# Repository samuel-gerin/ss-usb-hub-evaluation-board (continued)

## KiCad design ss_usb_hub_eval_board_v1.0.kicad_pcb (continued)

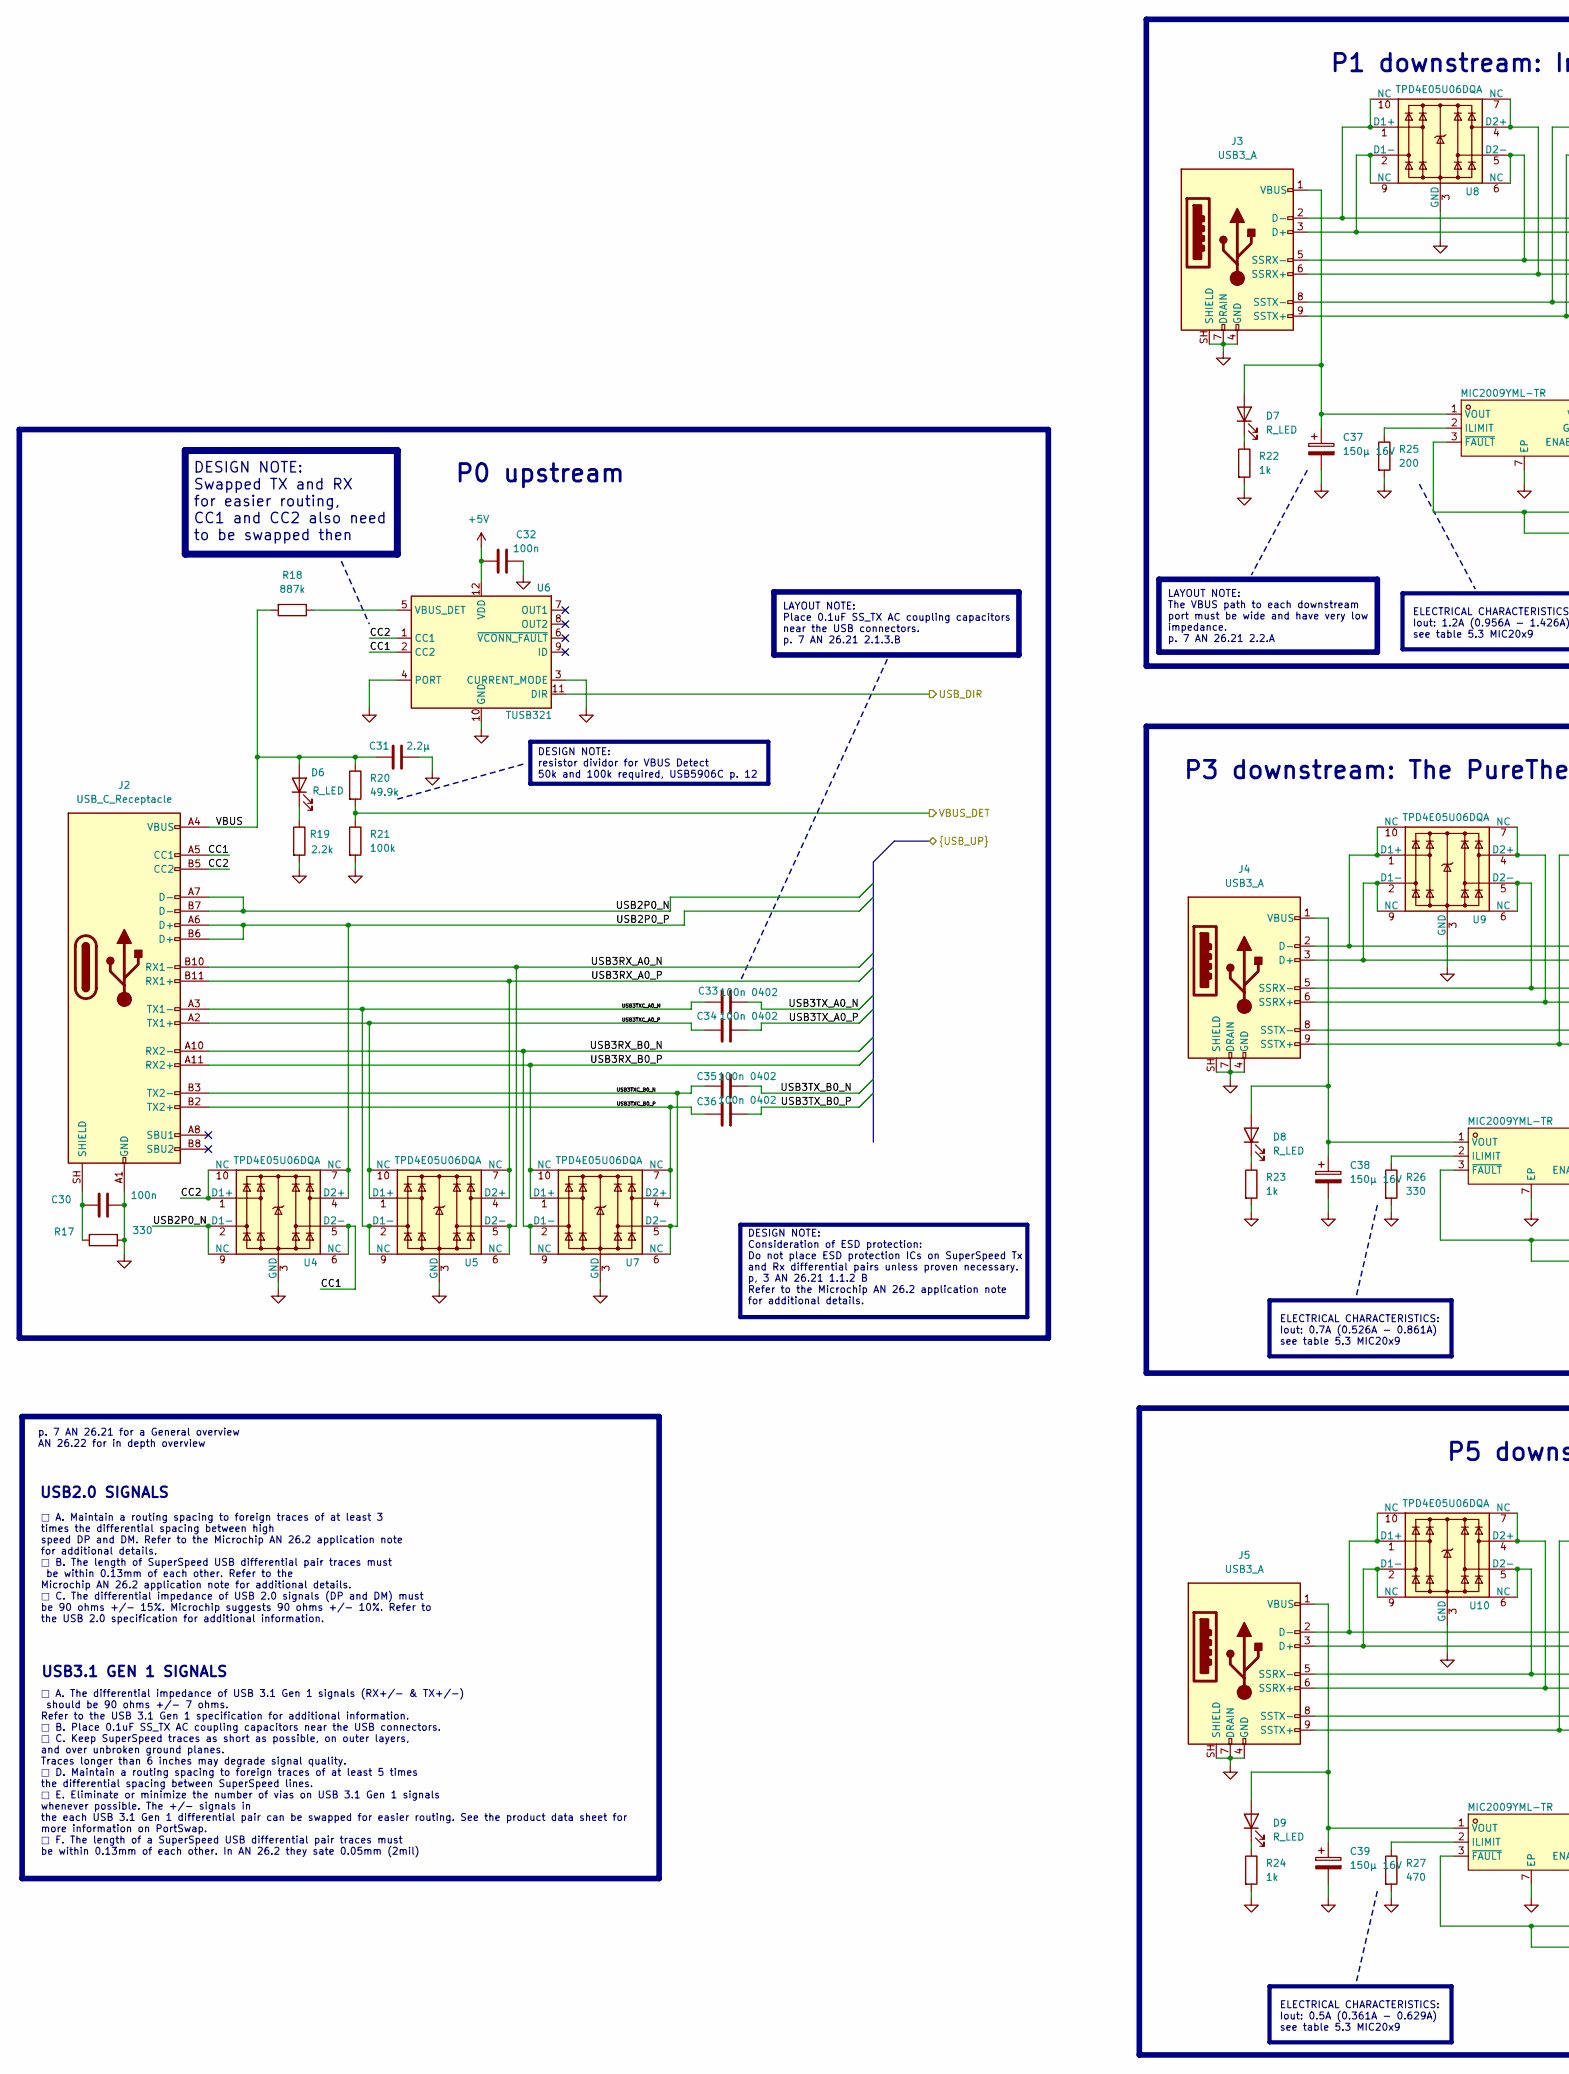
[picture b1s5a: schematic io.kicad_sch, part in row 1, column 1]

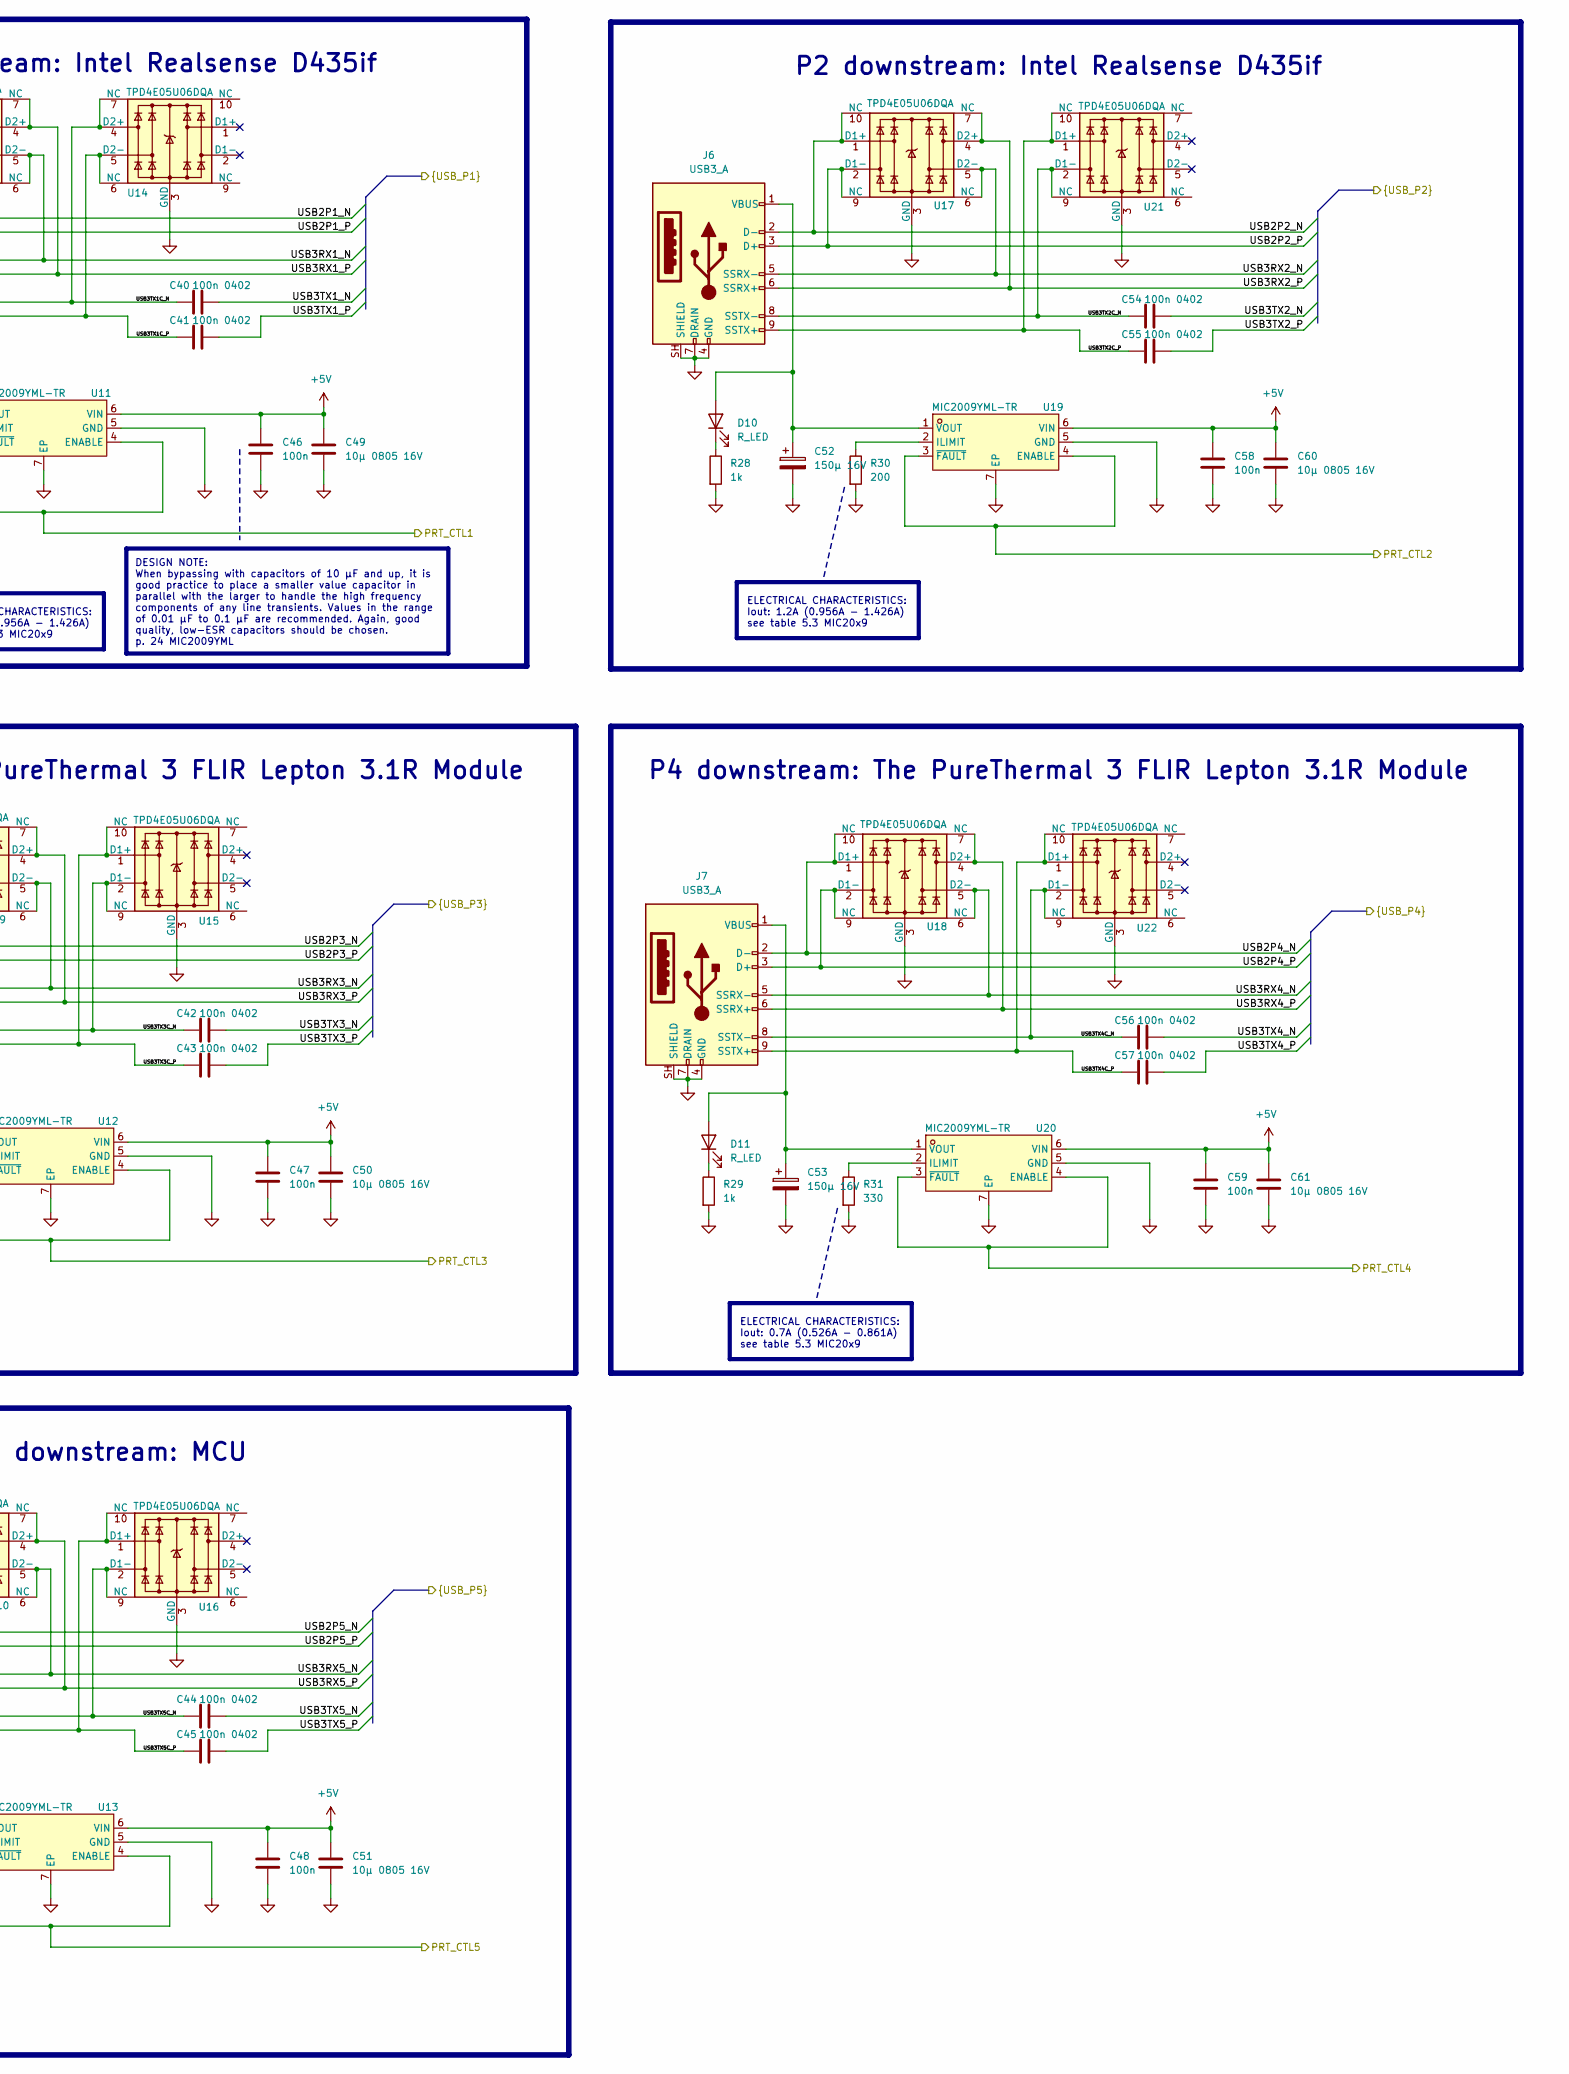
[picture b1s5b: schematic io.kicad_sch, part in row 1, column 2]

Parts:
C30, C32, C46, C47, C48, C58, C59: 100n; C_0603_1608Metric; LCSC C14663
C31: 2.2µ; C_0603_1608Metric; LCSC C23630
C33, C34, C35, C36, C40, C41, C42, C43, C44, C45, C54, C55, C56, C57: 100n 0402; C_0402_1005Metric; LCSC C1525
C37, C38, C52, C53: 150µ 16V; CP_Elec_8x10; LCSC C38513
C39: 150µ 16V; CP_Elec_8x10.5; LCSC C38513
C49, C50, C51, C60, C61: 10µ 0805 16V; C_0805_2012Metric; LCSC C1713
D6, D7, D8, D9, D10, D11: R_LED; LED_0603_1608Metric; LCSC C2286
J2: USB_C_Receptacle; USB-C-SMD_TYPE-C-USB-18; LCSC C134092
J3, J4, J5, J6, J7: USB3_A; USB-SMD_692122030100; LCSC C5355286
R17, R26, R31: 330; R_0603_1608Metric; LCSC C23138
R18: 887k; R_0603_1608Metric; LCSC C246015
R19: 2.2k; R_0603_1608Metric; LCSC C4190
R20: 49.9k; R_0603_1608Metric; LCSC C23184
R21: 100k; R_0603_1608Metric; LCSC C25803
R22, R23, R24, R28, R29: 1k; R_0603_1608Metric; LCSC C21190
R25, R30: 200; R_0603_1608Metric; LCSC C8218
R27: 470; R_0603_1608Metric; LCSC C23179
U4, U5, U7, U8, U9, U10, U14, U15, U16, U17, U18, U21, U22: TPD4E05U06DQA; USON-10_2.5x1.0mm_P0.5mm; LCSC C138714
U6: TUSB321; Texas_X2QFN-12_1.6x1.6mm_P0.4mm; LCSC C139392
U11, U12, U13, U19, U20: MIC2009YML-TR; MLF-6_L2.0-W2.0-P0.65-BL-EP; MPN MIC2009YML-TR; LCSC Part C621495

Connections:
+5V: C32.2, C46.1, C47.1, C48.1, C49.1, C50.1, C51.1, C58.1, C59.1, C60.1, C61.1, U6.12 (VDD), U11.6 (VIN), U12.6 (VIN), U13.6 (VIN), U19.6 (VIN), U20.6 (VIN); also elsewhere on the board
/IO/CC1: J2.A5 (CC1), U4.5 (D2-), U4.6 (NC), U6.2 (CC2)
/IO/CC2: J2.B5 (CC2), U4.1 (D1+), U4.10 (NC), U6.1 (CC1)
/IO/PRT_CTL1: U11.3 (~FAULT), U11.4 (ENABLE); also elsewhere on the board
/IO/PRT_CTL2: U19.3 (~FAULT), U19.4 (ENABLE); also elsewhere on the board
/IO/PRT_CTL3: U12.3 (~FAULT), U12.4 (ENABLE); also elsewhere on the board
/IO/PRT_CTL4: U20.3 (~FAULT), U20.4 (ENABLE); also elsewhere on the board
/IO/PRT_CTL5: U13.3 (~FAULT), U13.4 (ENABLE); also elsewhere on the board
/IO/USB2P0_N: J2.A7 (D-), J2.B7 (D-), U4.2 (D1-), U4.9 (NC); also elsewhere on the board
/IO/USB2P0_P: J2.A6 (D+), J2.B6 (D+), U4.4 (D2+), U4.7 (NC); also elsewhere on the board
/IO/USB2P1_N: J3.2 (D-), U8.1 (D1+), U8.10 (NC); also elsewhere on the board
/IO/USB2P1_P: J3.3 (D+), U8.2 (D1-), U8.9 (NC); also elsewhere on the board
/IO/USB2P2_N: J6.2 (D-), U17.1 (D1+), U17.10 (NC); also elsewhere on the board
/IO/USB2P2_P: J6.3 (D+), U17.2 (D1-), U17.9 (NC); also elsewhere on the board
/IO/USB2P3_N: J4.2 (D-), U9.1 (D1+), U9.10 (NC); also elsewhere on the board
/IO/USB2P3_P: J4.3 (D+), U9.2 (D1-), U9.9 (NC); also elsewhere on the board
/IO/USB2P4_N: J7.2 (D-), U18.1 (D1+), U18.10 (NC); also elsewhere on the board
/IO/USB2P4_P: J7.3 (D+), U18.2 (D1-), U18.9 (NC); also elsewhere on the board
/IO/USB2P5_N: J5.2 (D-), U10.1 (D1+), U10.10 (NC); also elsewhere on the board
/IO/USB2P5_P: J5.3 (D+), U10.2 (D1-), U10.9 (NC); also elsewhere on the board
/IO/USB3RX1_N: J3.5 (SSRX-), U8.5 (D2-), U8.6 (NC); also elsewhere on the board
/IO/USB3RX1_P: J3.6 (SSRX+), U8.4 (D2+), U8.7 (NC); also elsewhere on the board
/IO/USB3RX2_N: J6.5 (SSRX-), U17.5 (D2-), U17.6 (NC); also elsewhere on the board
/IO/USB3RX2_P: J6.6 (SSRX+), U17.4 (D2+), U17.7 (NC); also elsewhere on the board
/IO/USB3RX3_N: J4.5 (SSRX-), U9.5 (D2-), U9.6 (NC); also elsewhere on the board
/IO/USB3RX3_P: J4.6 (SSRX+), U9.4 (D2+), U9.7 (NC); also elsewhere on the board
/IO/USB3RX4_N: J7.5 (SSRX-), U18.5 (D2-), U18.6 (NC); also elsewhere on the board
/IO/USB3RX4_P: J7.6 (SSRX+), U18.4 (D2+), U18.7 (NC); also elsewhere on the board
/IO/USB3RX5_N: J5.5 (SSRX-), U10.5 (D2-), U10.6 (NC); also elsewhere on the board
/IO/USB3RX5_P: J5.6 (SSRX+), U10.4 (D2+), U10.7 (NC); also elsewhere on the board
/IO/USB3RX_A0_N: J2.B10 (RX1-), U5.5 (D2-), U5.6 (NC); also elsewhere on the board
/IO/USB3RX_A0_P: J2.B11 (RX1+), U5.4 (D2+), U5.7 (NC); also elsewhere on the board
/IO/USB3RX_B0_N: J2.A10 (RX2-), U7.2 (D1-), U7.9 (NC); also elsewhere on the board
/IO/USB3RX_B0_P: J2.A11 (RX2+), U7.1 (D1+), U7.10 (NC); also elsewhere on the board
/IO/USB3TX1C_N: C40.1, J3.8 (SSTX-), U14.4 (D2+), U14.7 (NC)
/IO/USB3TX1C_P: C41.1, J3.9 (SSTX+), U14.5 (D2-), U14.6 (NC)
/IO/USB3TX1_N: C40.2; also elsewhere on the board
/IO/USB3TX1_P: C41.2; also elsewhere on the board
/IO/USB3TX2C_N: C54.1, J6.8 (SSTX-), U21.2 (D1-), U21.9 (NC)
/IO/USB3TX2C_P: C55.1, J6.9 (SSTX+), U21.1 (D1+), U21.10 (NC)
/IO/USB3TX2_N: C54.2; also elsewhere on the board
/IO/USB3TX2_P: C55.2; also elsewhere on the board
/IO/USB3TX3C_N: C42.1, J4.8 (SSTX-), U15.2 (D1-), U15.9 (NC)
/IO/USB3TX3C_P: C43.1, J4.9 (SSTX+), U15.1 (D1+), U15.10 (NC)
/IO/USB3TX3_N: C42.2; also elsewhere on the board
/IO/USB3TX3_P: C43.2; also elsewhere on the board
/IO/USB3TX4C_N: C56.1, J7.8 (SSTX-), U22.2 (D1-), U22.9 (NC)
/IO/USB3TX4C_P: C57.1, J7.9 (SSTX+), U22.1 (D1+), U22.10 (NC)
/IO/USB3TX4_N: C56.2; also elsewhere on the board
/IO/USB3TX4_P: C57.2; also elsewhere on the board
/IO/USB3TX5C_N: C44.1, J5.8 (SSTX-), U16.2 (D1-), U16.9 (NC)
/IO/USB3TX5C_P: C45.1, J5.9 (SSTX+), U16.1 (D1+), U16.10 (NC)
/IO/USB3TX5_N: C44.2; also elsewhere on the board
/IO/USB3TX5_P: C45.2; also elsewhere on the board
/IO/USB3TXC_A0_N: C33.1, J2.A3 (TX1-), U5.2 (D1-), U5.9 (NC)
/IO/USB3TXC_A0_P: C34.1, J2.A2 (TX1+), U5.1 (D1+), U5.10 (NC)
/IO/USB3TXC_B0_N: C35.1, J2.B3 (TX2-), U7.5 (D2-), U7.6 (NC)
/IO/USB3TXC_B0_P: C36.1, J2.B2 (TX2+), U7.4 (D2+), U7.7 (NC)
/IO/USB3TX_A0_N: C33.2; also elsewhere on the board
/IO/USB3TX_A0_P: C34.2; also elsewhere on the board
/IO/USB3TX_B0_N: C35.2; also elsewhere on the board
/IO/USB3TX_B0_P: C36.2; also elsewhere on the board
/IO/USB_DIR: U6.11 (DIR); also elsewhere on the board
/IO/VBUS: C31.2, D6.2 (A), J2.A4 (VBUS), J2.A9 (VBUS), J2.B4 (VBUS), J2.B9 (VBUS), R18.2, R20.1
/IO/VBUS_DET: R20.2, R21.1; also elsewhere on the board
GND: C30.1, C31.1, C32.1, C37.2, C38.2, C39.2, C46.2, C47.2, C48.2, C49.2, C50.2, C51.2, C52.2, C53.2, C58.2, C59.2, C60.2, C61.2, J2.A1 (GND), J2.A12 (GND), J2.B1 (GND), J2.B12 (GND), J3.4 (GND), J3.7 (DRAIN), J3.SH (SHIELD), J4.4 (GND), J4.7 (DRAIN), J4.SH (SHIELD), J5.4 (GND), J5.7 (DRAIN), J5.SH (SHIELD), J6.4 (GND), J6.7 (DRAIN), J6.SH (SHIELD), J7.4 (GND), J7.7 (DRAIN), J7.SH (SHIELD), R17.2, R19.2, R21.2, R22.2, R23.2, R24.2, R25.2, R26.2, R27.2, R28.2, R29.2, R30.2, R31.2, U4.3 (GND), U4.8 (GND), U5.3 (GND), U5.8 (GND), U6.3 (CURRENT_MODE), U6.4 (PORT), U6.10 (GND), U7.3 (GND), U7.8 (GND), U8.3 (GND), U8.8 (GND), U9.3 (GND), U9.8 (GND), U10.3 (GND), U10.8 (GND), U11.5 (GND), U11.7 (EP), U12.5 (GND), U12.7 (EP), U13.5 (GND), U13.7 (EP), U14.3 (GND), U14.8 (GND), U15.3 (GND), U15.8 (GND), U16.3 (GND), U16.8 (GND), U17.3 (GND), U17.8 (GND), U18.3 (GND), U18.8 (GND), U19.5 (GND), U19.7 (EP), U20.5 (GND), U20.7 (EP), U21.3 (GND), U21.8 (GND), U22.3 (GND), U22.8 (GND); also elsewhere on the board
unnamed: D6.1 (K), R19.1
unnamed: C37.1, D7.2 (A), J3.1 (VBUS), U11.1 (VOUT)
unnamed: D7.1 (K), R22.1
unnamed: C38.1, D8.2 (A), J4.1 (VBUS), U12.1 (VOUT)
unnamed: D8.1 (K), R23.1
unnamed: C39.1, D9.2 (A), J5.1 (VBUS), U13.1 (VOUT)
unnamed: D9.1 (K), R24.1
unnamed: C52.1, D10.2 (A), J6.1 (VBUS), U19.1 (VOUT)
unnamed: D10.1 (K), R28.1
unnamed: C53.1, D11.2 (A), J7.1 (VBUS), U20.1 (VOUT)
unnamed: D11.1 (K), R29.1
unnamed: C30.2, J2.SH (SHIELD), R17.1
unnamed: R18.1, U6.5 (VBUS_DET)
unnamed: R25.1, U11.2 (ILIMIT)
unnamed: R26.1, U12.2 (ILIMIT)
unnamed: R27.1, U13.2 (ILIMIT)
unnamed: R30.1, U19.2 (ILIMIT)
unnamed: R31.1, U20.2 (ILIMIT)

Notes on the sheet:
DESIGN NOTE: Swapped TX and RX for easier routing, CC1 and CC2 also need to be swapped then
DESIGN NOTE: resistor dividor for VBUS Detect 50k and 100k required, USB5906C p. 12
USB2.0 SIGNALS
DESIGN NOTE: Consideration of ESD protection: Do not place ESD protection ICs on SuperSpeed Tx and Rx differential pairs unless proven necessary. p, 3 AN 26.21 1.1.2 B Refer to the Microchip AN 26.2 application note for additional details.
LAYOUT NOTE: The VBUS path to each downstream port must be wide and have very low impedance. p. 7 AN 26.21 2.2.A
P4 downstream: The PureThermal 3 FLIR Lepton 3.1R Module
ELECTRICAL CHARACTERISTICS: Iout: 0.5A (0.361A - 0.629A) see table 5.3 MIC20x9
ELECTRICAL CHARACTERISTICS: Iout: 1.2A (0.956A - 1.426A) see table 5.3 MIC20x9
ELECTRICAL CHARACTERISTICS: Iout: 0.7A (0.526A - 0.861A) see table 5.3 MIC20x9
P2 downstream: Intel Realsense D435if
P5 downstream: MCU
□ A. The differential impedance of USB 3.1 Gen 1 signals (RX+/- & TX+/-) should be 90 ohms +/- 7 ohms. Refer to the USB 3.1 Gen 1 specification for additional information. □ B. Place 0.1uF SS_TX AC coupling capacitors near the USB connectors. □ C. Keep SuperSpeed traces as short as possible, on out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
□ A. Maintain a routing spacing to foreign traces of at least 3 times the differential spacing between high speed DP and DM. Refer to the Microchip AN 26.2 application note for additional details. □ B. The length of SuperSpeed USB differential pair traces must be within 0.13mm of each other. Refer 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
LAYOUT NOTE: Place 0.1uF SS_TX AC coupling capacitors near the USB connectors. p. 7 AN 26.21 2.1.3.B
P3 downstream: The PureThermal 3 FLIR Lepton 3.1R Module
P1 downstream: Intel Realsense D435if
P0 upstream
DESIGN NOTE: When bypassing with capacitors of 10 μF and up, it is good practice to place a smaller value capacitor in parallel with the larger to handle the high frequency components of any line transients. Values in the range of 0.01 μF to 0.1 μF are recommended. Again, good quality, low-ESR capa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
USB3.1 GEN 1 SIGNALS
p. 7 AN 26.21 for a General overview AN 26.22 for in depth overview

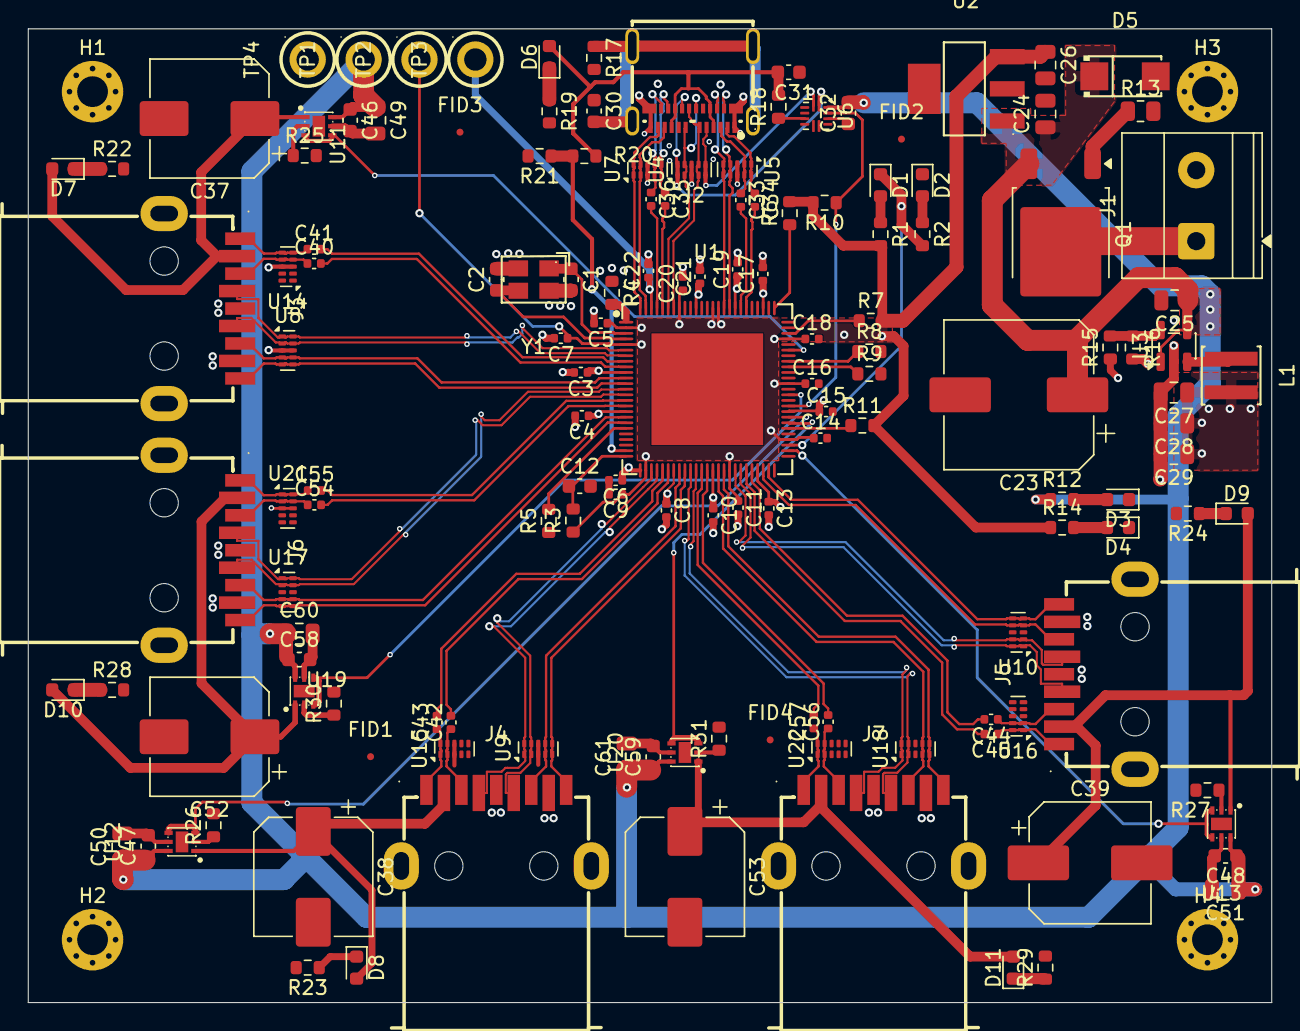
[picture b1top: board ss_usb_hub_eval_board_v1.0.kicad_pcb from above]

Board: 4 copper layers, 89.0 x 69.7 mm, 147 parts (0 on the bottom side), 105 nets.
